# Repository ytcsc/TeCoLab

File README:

TeCoLab stands for Temperature Control Laboratory. It is an open source platform that contains (Arduino Nano compatible) hardware, firmware (Arduino Nano) and software (Python). The purpose of this project is to provide a cheap platform to help any interested person to understand several basic concepts about control systems. This project uses a MIT License, which means that you are basically free to do anything you like with this project.

All documentation has been moved to the (Wiki)[https://github.com/ytcsc/TeCoLab/wiki]!

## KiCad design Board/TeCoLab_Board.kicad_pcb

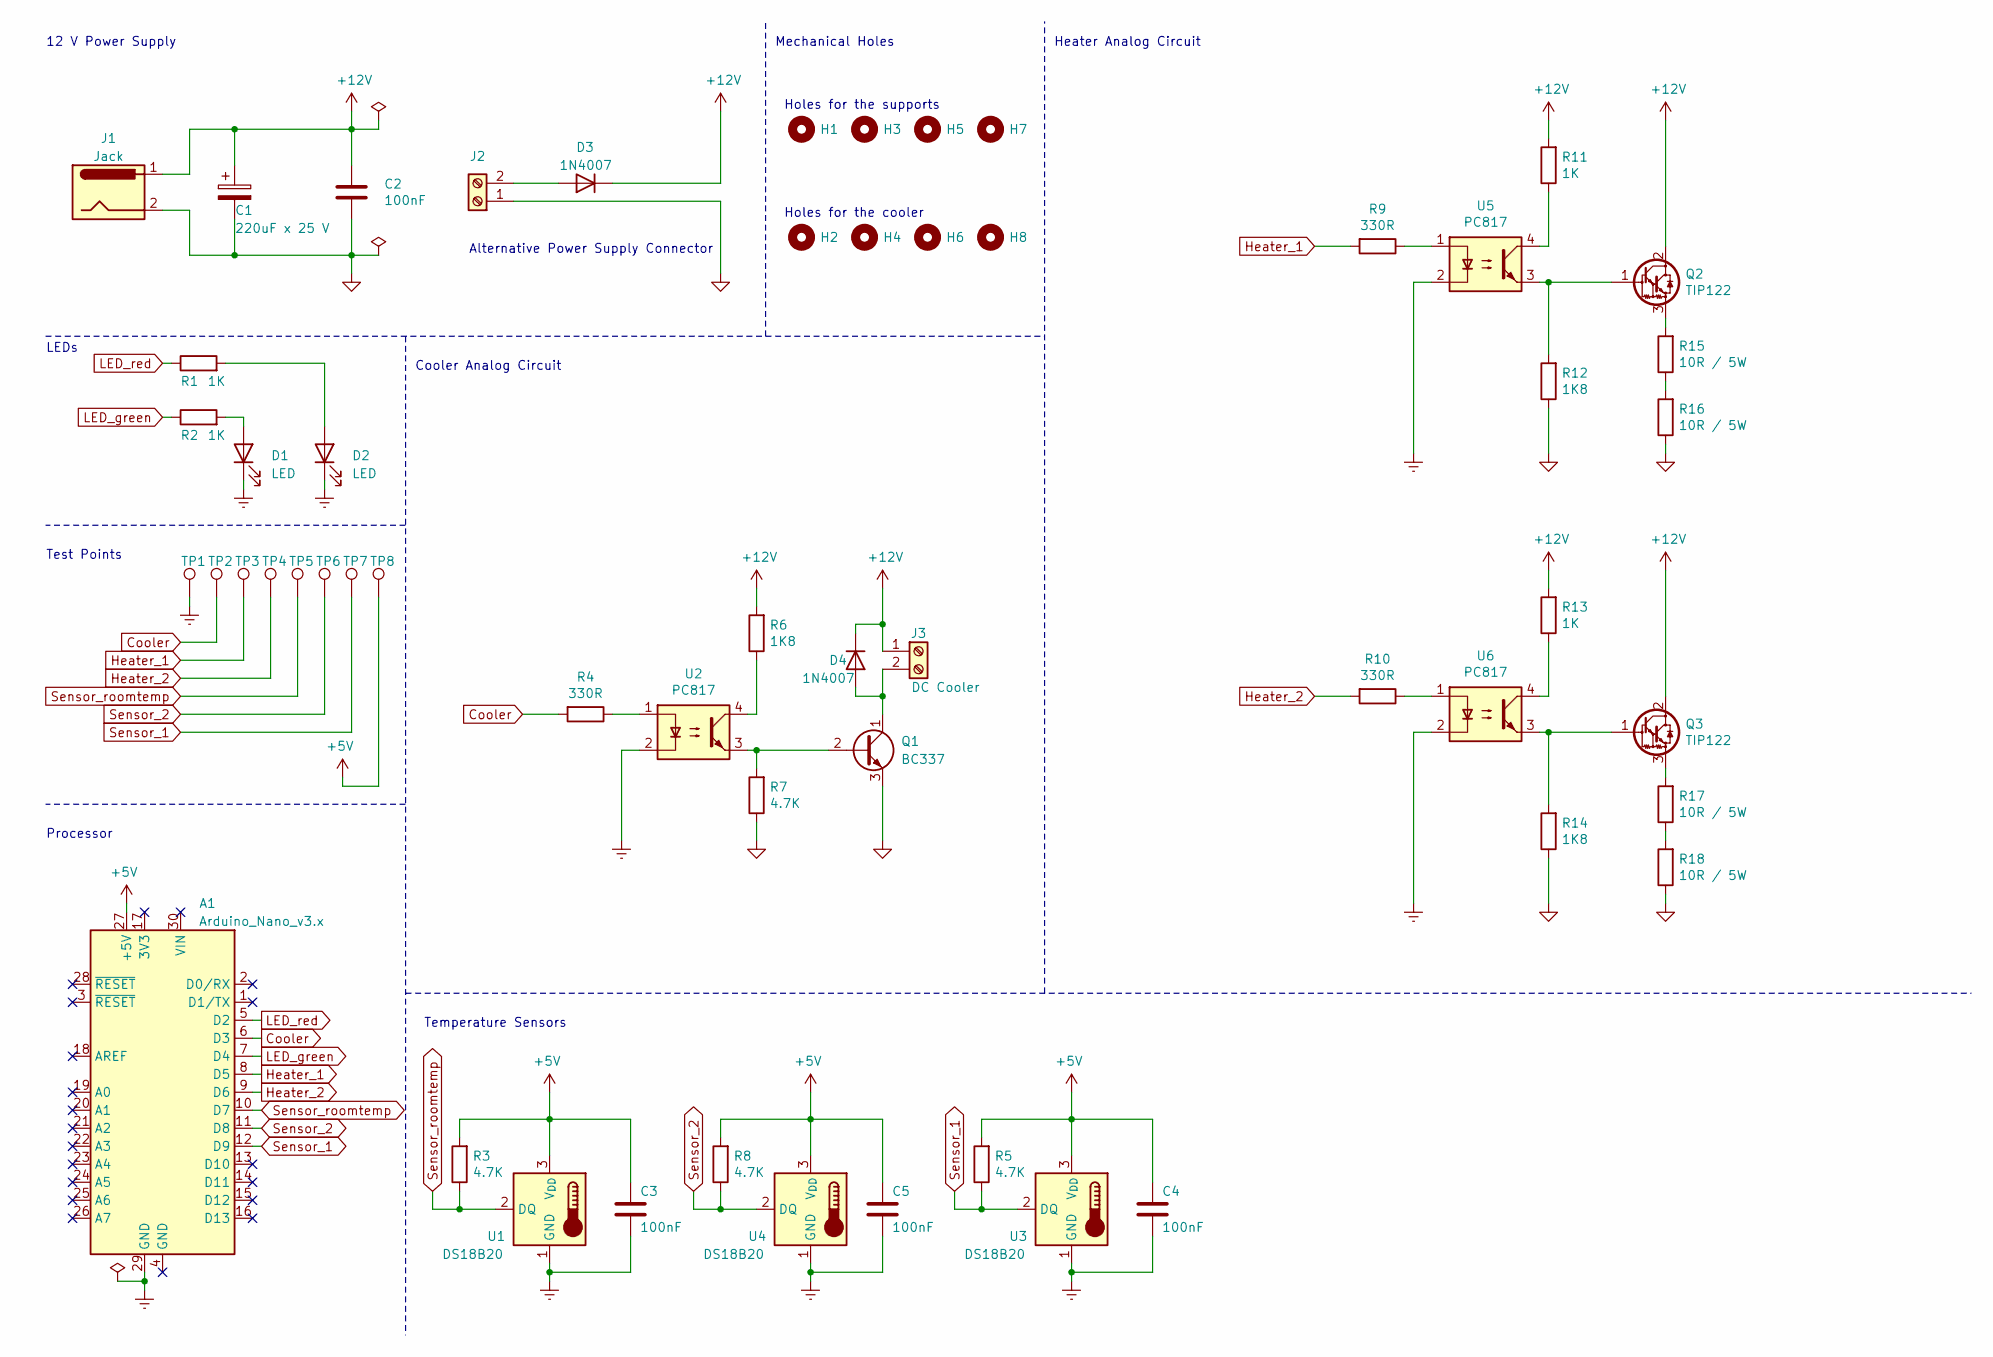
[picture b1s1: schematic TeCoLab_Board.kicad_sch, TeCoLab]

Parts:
A1: Arduino_Nano_v3.x; Arduino_Nano
C1: 220uF x 25 V; CP_Radial_D8.0mm_P3.50mm
C2, C3, C4, C5: 100nF; C_Rect_L7.0mm_W2.0mm_P5.00mm
D1, D2: LED; LED_D3.0mm
D3, D4: 1N4007; D_DO-41_SOD81_P10.16mm_Horizontal
H1, H3, H5, H7: Hole; MountingHole_6mm
H2, H4, H6, H8: Hole; MountingHole_3.2mm_M3
J1: Jack; BarrelJack_Horizontal
J2: Supply_Terminal; TerminalBlock_bornier-2_P5.08mm
J3: DC Cooler; TerminalBlock_bornier-2_P5.08mm
Q1: BC337; TO-92_HandSolder
Q2, Q3: TIP122; TO-220-3_Vertical
R1, R2, R11, R13: 1K; R_Axial_DIN0207_L6.3mm_D2.5mm_P7.62mm_Horizontal
R3, R5, R7, R8: 4.7K; R_Axial_DIN0207_L6.3mm_D2.5mm_P7.62mm_Horizontal
R4, R9, R10: 330R; R_Axial_DIN0207_L6.3mm_D2.5mm_P7.62mm_Horizontal
R6, R12, R14: 1K8; R_Axial_DIN0207_L6.3mm_D2.5mm_P7.62mm_Horizontal
R15, R16, R17, R18: 10R / 5W; R_Axial_DIN0617_L17.0mm_D6.0mm_P20.32mm_Horizontal
TP1, TP2, TP3, TP4, TP5, TP6, TP7, TP8: TestPoint; TestPoint_THTPad_D1.0mm_Drill0.5mm
U1, U3, U4: DS18B20; TO-92_HandSolder
U2, U5, U6: PC817; DIP-4_W7.62mm

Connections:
+5V: A1.27 (+5V), C3.1, C4.1, C5.1, R3.2, R5.2, R8.2, TP8.1, U1.3 (V_{DD}), U3.3 (V_{DD}), U4.3 (V_{DD})
+12V: C1.1, C2.1, D3.1 (K), D4.1 (K), J1.1, J3.1, Q2.2 (C), Q3.2 (C), R6.2, R11.2, R13.2
Cooler: A1.6 (D3), R4.2, TP2.1
GND: C1.2, C2.2, J1.2, J2.1, Q1.3 (E), R7.1, R12.1, R14.1, R16.1, R18.1
GNDREF: A1.29 (GND), C3.2, C4.2, C5.2, D1.1 (K), D2.1 (K), TP1.1, U1.1 (GND), U2.2, U3.1 (GND), U4.1 (GND), U5.2, U6.2
Heater_1: A1.8 (D5), R9.2, TP3.1
Heater_2: A1.9 (D6), R10.2, TP4.1
LED_green: A1.7 (D4), R2.1
LED_red: A1.5 (D2), R1.1
unnamed: D1.2 (A), R2.2
unnamed: D2.2 (A), R1.2
unnamed: D3.2 (A), J2.2
unnamed: D4.2 (A), J3.2, Q1.1 (C)
unnamed: Q1.2 (B), R7.2, U2.3
unnamed: Q2.1 (B), R12.2, U5.3
unnamed: Q2.3 (E), R15.2
unnamed: Q3.1 (B), R14.2, U6.3
unnamed: Q3.3 (E), R17.2
unnamed: R4.1, U2.1
unnamed: R6.1, U2.4
unnamed: R9.1, U5.1
unnamed: R10.1, U6.1
unnamed: R11.1, U5.4
unnamed: R13.1, U6.4
unnamed: R15.1, R16.2
unnamed: R17.1, R18.2
Sensor_1: A1.12 (D9), R5.1, TP7.1, U3.2 (DQ)
Sensor_2: A1.11 (D8), R8.1, TP6.1, U4.2 (DQ)
Sensor_roomtemp: A1.10 (D7), R3.1, TP5.1, U1.2 (DQ)

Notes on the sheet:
Holes for the cooler
12 V Power Supply
Alternative Power Supply Connector
Mechanical Holes
LEDs
Test Points
Processor
Heater Analog Circuit
Temperature Sensors
Holes for the supports
Cooler Analog Circuit

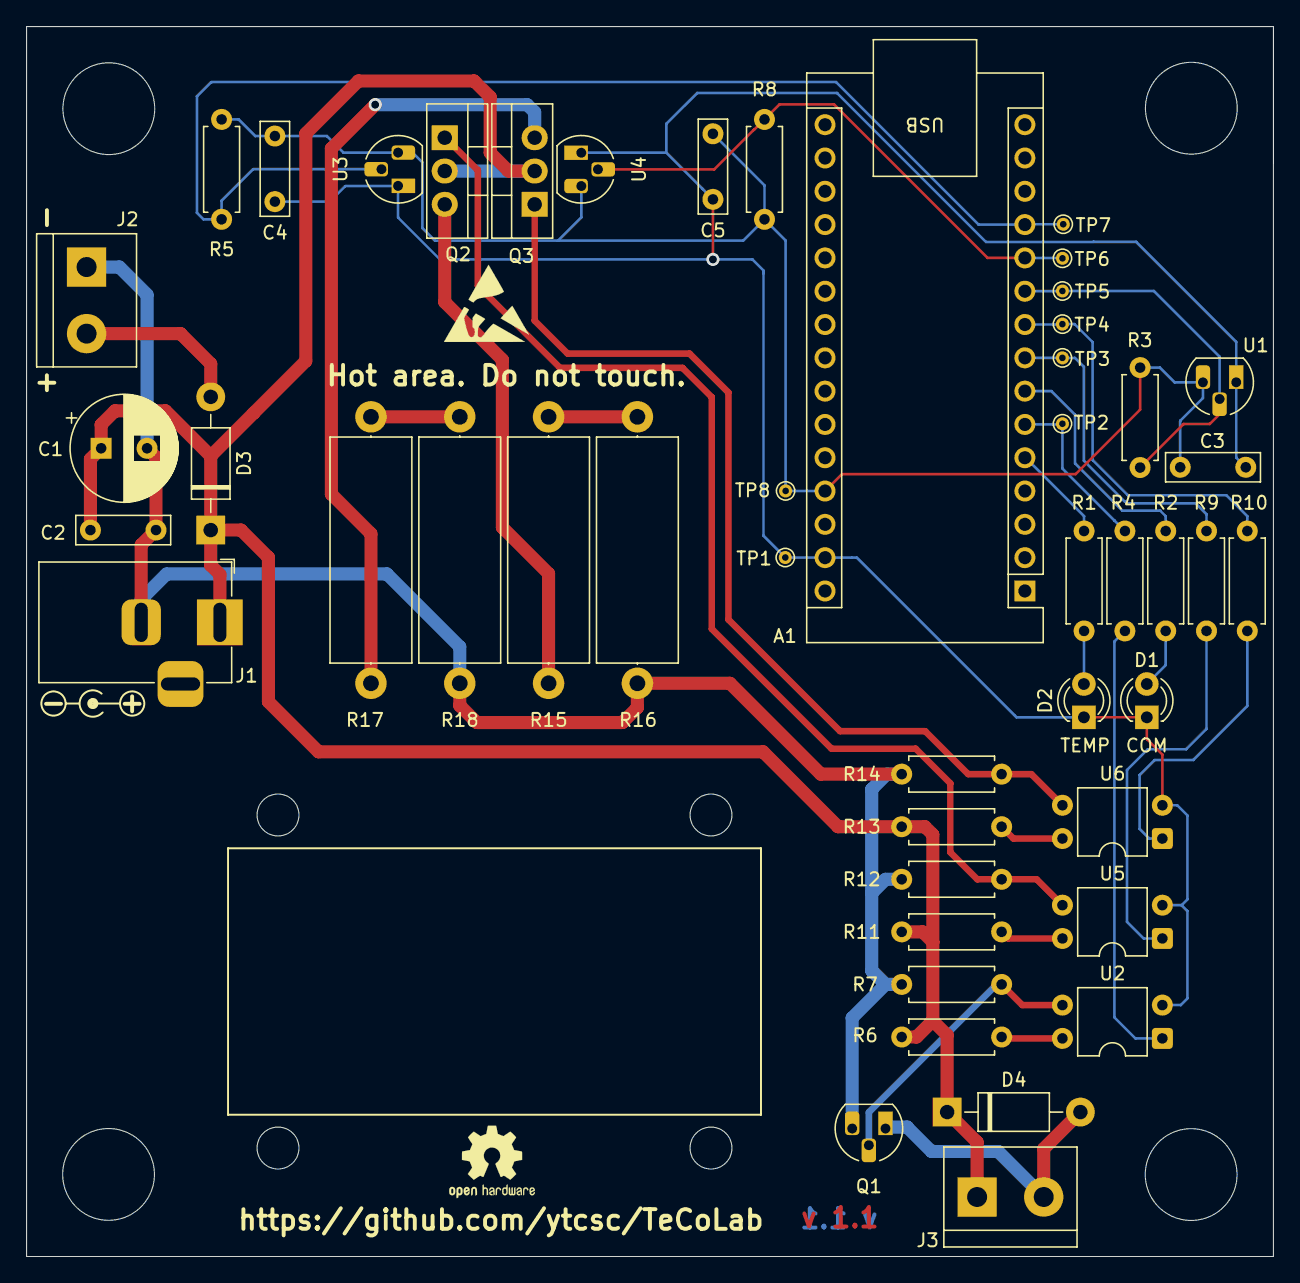
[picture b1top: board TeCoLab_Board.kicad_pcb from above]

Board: 2 copper layers, 95.1 x 93.8 mm, 56 parts (0 on the bottom side), 29 nets.

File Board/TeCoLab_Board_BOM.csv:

"Reference","Value","Footprint","Datasheet","Qty","DNP"
"A1","Arduino_Nano_v3.x","Module:Arduino_Nano","http://www.mouser.com/pdfdocs/Gravitech_Arduino_Nano3_0.pdf","1",""
"C1","220uF x 25 V","Capacitor_THT:CP_Radial_D8.0mm_P3.50mm","~","1",""
"C2,C3,C4,C5","100nF","Capacitor_THT:C_Rect_L7.0mm_W2.0mm_P5.00mm","~","4",""
"D1,D2","LED","LED_THT:LED_D3.0mm","~","2",""
"D3,D4","1N4007","Diode_THT:D_DO-41_SOD81_P10.16mm_Horizontal","http://www.vishay.com/docs/88503/1n4001.pdf","2",""
"H1,H2,H3,H4,H5,H6,H7,H8","Hole","MountingHole:MountingHole_3.2mm_M3,MountingHole:MountingHole_6mm","~","8",""
"J1","Jack","Connector_BarrelJack:BarrelJack_Horizontal","~","1",""
"J2","Supply_Terminal","TerminalBlock:TerminalBlock_bornier-2_P5.08mm","~","1",""
"J3","DC Cooler","TerminalBlock:TerminalBlock_bornier-2_P5.08mm","~","1",""
"Q1","BC337","Package_TO_SOT_THT:TO-92_HandSolder","https://diotec.com/tl_files/diotec/files/pdf/datasheets/bc337.pdf","1",""
"Q2,Q3","TIP122","Package_TO_SOT_THT:TO-220-3_Vertical","http://www.fairchildsemi.com/ds/TI/TIP120.pdf","2",""
"R1,R2,R11,R13","1K","Resistor_THT:R_Axial_DIN0207_L6.3mm_D2.5mm_P7.62mm_Horizontal","~","4",""
"R3,R5,R7,R8","4.7K","Resistor_THT:R_Axial_DIN0207_L6.3mm_D2.5mm_P7.62mm_Horizontal","~","4",""
"R4,R9,R10","330R","Resistor_THT:R_Axial_DIN0207_L6.3mm_D2.5mm_P7.62mm_Horizontal","~","3",""
"R6,R12,R14","1K8","Resistor_THT:R_Axial_DIN0207_L6.3mm_D2.5mm_P7.62mm_Horizontal","~","3",""
"R15,R16,R17,R18","10R / 5W","Resistor_THT:R_Axial_DIN0617_L17.0mm_D6.0mm_P20.32mm_Horizontal","~","4",""
"TP1,TP2,TP3,TP4,TP5,TP6,TP7,TP8","TestPoint","TestPoint:TestPoint_THTPad_D1.0mm_Drill0.5mm","~","8",""
"U1,U3,U4","DS18B20","Package_TO_SOT_THT:TO-92_HandSolder","http://datasheets.maximintegrated.com/en/ds/DS18B20.pdf","3",""
"U2,U5,U6","PC817","Package_DIP:DIP-4_W7.62mm","http://www.soselectronic.cz/a_info/resource/d/pc817.pdf","3",""

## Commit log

2021-10-30 Add files via upload
    Electronic schematic added
2021-10-30 Update README
    Minor changes in README file.
2021-10-30 Added english text in the schematic.
2021-10-30 Associated footprints and generated BOM.
2021-11-14 Changed some resistor's values due to excessive power dissipation.
2021-11-21 Schematic changes. Arduino NANO replaced Arduino UNO. Alternative power supply connector added. Mechanical holes added. TIP122 replaced discrete darlington pair. 100nF capacitors inserted in the powe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
2021-11-29 Schematic: added testpoints; the analog circuits were simplified; the cooler connector was changed. Firmware: first commit.
2021-12-11 Schematic: small changes to help the PCB design. PCB design: first commit. Corrections in the previous commit, since some files were not added.
2022-01-14 PCB design: PCB size reduction.
2022-01-22 PCB design: Final modifications before PCB manufacturing. The polarity of the DC Jack was changed since DC power supplies often have the positive terminal in the middle.
2022-01-27 PCB design: added PCB version on it.
2022-01-27 PCB: Gerbers added.
2022-02-28 Firmware: small bug correction regarding connectionStatus.
2022-03-27 Firmware: Increased Baudrate from 9600 to 115200 to enhance performance.
2022-03-29 Software: First release.
2022-04-02 PCB: Mounting holes updated to 7 mm. TeCoLab logo resized to 70 percent of the previous size.
2022-04-02 Software: Log file is no longer saved with the Pandas' index as first column. Moreover, each experiment must have a .txt file with its description to be displayed by the software during the experimen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
2022-04-30 Software: Changed method to save the csv log file using append in order to speed this process up.
2022-05-01 Software: fundamental period of experiment changed from 100 ms to 200 ms for more stable performance.
2022-05-23 Software: Added step response experiment and Octave script to analyse this experiment.
2022-07-30 Software: corrected bugs in NullControl, which would impact the implementation of new controllers.
2022-08-23 Software: changed log file name to be compatible with Windows OS.
2022-09-10 Software: Implemented command line arguments. Now, the experiment file and the controller module name must be passed as arguments.
2023-01-22 Software: Implemented kwargs in NullControl.
2023-08-19 columns name modified
2023-08-19 Update README
    Substituted Arduino UNO with Arduino NANO, as the latter board was employed during the development.
2023-08-21 FIle directory changed
2023-08-26 Schematic: swap of the two labels named Sensor1 and Sensor2. This changes nothing in the PCB layout, but the files were checked as well and saved, generating a new version of them too. Firmware: chan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
2023-09-23 step response script
2023-09-23 remove useless code in step response script
2023-10-05 step_response_identification fixed
2023-12-02 Feat/step response identification (#8)
    * step response script
    * remove useless code in step response script
    * step_response_identification fixed
    * Update step_response_identification.py
2023-12-31 Firmware: when the board loses connection with the computer, the actuators are turned off. Software: major changes. Renamed files, introduced rate of change limitation for the actuators as a disturba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
2023-12-31 Software: Removed unnecessary files.
2023-12-31 Main Branch Major Update (#12)
    * columns name modified
    * Update README
    Substituted Arduino UNO with Arduino NANO, as the latter board was employed during the development.
    * FIle directory changed
    * Schematic: swap of the two labels named Sensor1 and Sensor2. This changes nothing in the PCB layout, but the files were checked as well and saved, generating a new version of them too. Firmware: ch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
    * Feat/step response identification (#8)
2023-12-31 Software: Updating tecolab.py software.
2023-12-31 Main Branch Major Update (Correction) (#13)
    * columns name modified
    * Update README
    Substituted Arduino UNO with Arduino NANO, as the latter board was employed during the development.
    * FIle directory changed
    * Schematic: swap of the two labels named Sensor1 and Sensor2. This changes nothing in the PCB layout, but the files were checked as well and saved, generating a new version of them too. Firmware: ch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
    * Feat/step response identification (#8)
2023-12-31 Firmware: updating firwmare after forgetting to add this file to the commit.
2023-12-31 Main Branch Major Update (Correction) (#14)
    * columns name modified
    * Update README
    Substituted Arduino UNO with Arduino NANO, as the latter board was employed during the development.
    * FIle directory changed
    * Schematic: swap of the two labels named Sensor1 and Sensor2. This changes nothing in the PCB layout, but the files were checked as well and saved, generating a new version of them too. Firmware: ch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
    * Feat/step response identification (#8)
2025-02-22 Hardware: Update files to comply with KiCad version 8.0.
2025-04-19 Software: Update dependency handling and experiment logging
    - Added requirements.txt for managing Python dependencies
    - Updated Manual.tex and Manual.pdf to reflect new setup instructions
    - Modified tecolab_experiment.py to handle future pandas concat behavior
    - Added rate saturation fields to StepResponse.csv header
2025-04-20 Software: Correct bug where log file was not saving relative setpoint for sensor 2.
2025-04-26 Manual: Remove the manual. Documentation has been moved to the Wiki.
2025-06-28 Fix incorrect condition logic for low-temperature status detection (#17)
2025-07-07 Fix incorrect condition logic for low-temperature status detection (#17) (#18)
2025-07-07 Software: fix potential unbound variable error when searching serial ports.
2025-07-07 Software: add initial GUI for experiment configuration and real-time plotting.
2025-07-18 Update for KiCad 9.0 compatibility; remove gerbers from repository; Schematic: replaced 10K resistors by 4.7K resistors; PCB: replaced TO-92 package by its hand-soldering version.
2025-07-18 Main Branch Major Update (#19)
    * Hardware: Update files to comply with KiCad version 8.0.
    * Software: Update dependency handling and experiment logging
    - Added requirements.txt for managing Python dependencies
    - Updated Manual.tex and Manual.pdf to reflect new setup instructions
    - Modified tecolab_experiment.py to handle future pandas concat behavior
    - Added rate saturation fields to StepResponse.csv header
